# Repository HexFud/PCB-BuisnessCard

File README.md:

## PCB-Badge

I built this electronic badge that can be used for example in hachatons or other IT event if you open the project on KICAD you can also customize the writings.

## How this was made

This project consists only of one PCB 85x100mm and other components like the led matrix controller the microcontoller etc. It also has a NFC tag that can be written with the microcontroller and 2 minigames showed on the 8x8 led matrix on the front.

## How to flash the firmware

1. Install Arduino IDE
   
2. Add the board package going into File -> Preferences and in the additional board URL you paste this https://raw.githubusercontent.com/DeqingSun/ch55xduino/ch55xduino/package_ch55xduino_mcs51_index.json
  
3. Navigate to Tools -> Board -> Boards Manager search ch55xduino and click install
   
4. Plug the microcontroller into the pc and select the correct board you are using in my case a CH552
   
5. You can now flash the firmware

## Notes

If you want to bring your own game on the PCB you're welcome! just fork this repository and then if i'll like your work i am going to mention you guys in the original code. Unfortunatley we only have 2 buttons but in the future I can design another PCB with more functions

## AI decleration

Ai helped me to build the part of the firmware that controls the LED matrix

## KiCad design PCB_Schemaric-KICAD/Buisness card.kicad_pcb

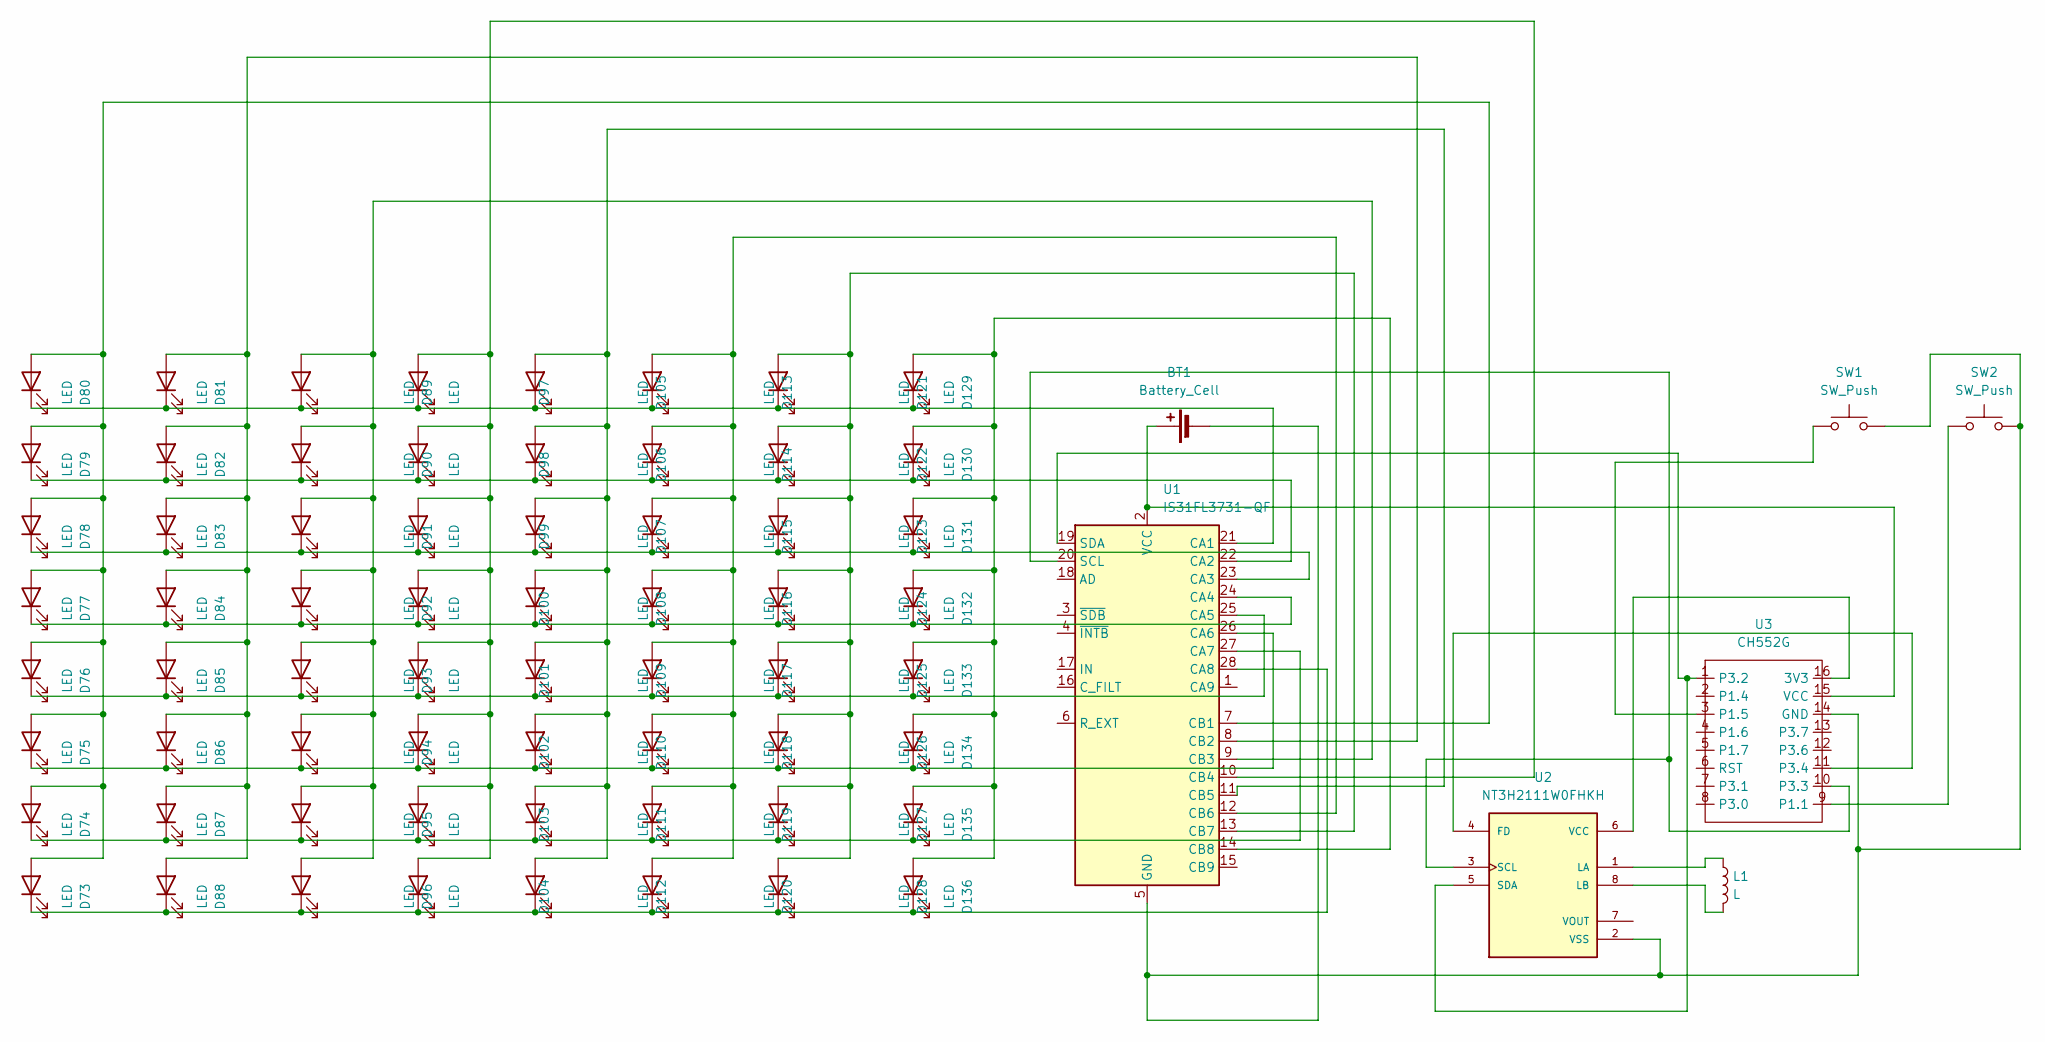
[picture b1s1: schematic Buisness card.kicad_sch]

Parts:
BT1: Battery_Cell; BatteryHolder_Keystone_103_1x20mm
D73, D74, D75, D76, D77, D78, D79, D80, D81, D82, D83, D84, D85, D86, D87, D88, D89, D90, D91, D92, D93, D94, D95, D96, D97, D98, D99, D100, D101, D102, D103, D104, D105, D106, D107, D108, D109, D110, D111, D112, D113, D114, D115, D116, D117, D118, D119, D120, D121, D122, D123, D124, D125, D126, D127, D128, D129, D130, D131, D132, D133, D134, D135, D136: LED; LED_1206_3216Metric
L1: L; COIL_GENERATOR
SW1, SW2: SW_Push; SW_TH_Tactile_Omron_B3F-102x
U1: IS31FL3731-QF; QFN-28-1EP_4x4mm_P0.4mm_EP2.3x2.3mm
U2: NT3H2111W0FHKH; QFN8P50_160X160X50L40X20N
U3: CH552G

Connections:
unnamed: BT1.1 (+), U1.2 (VCC), U3.15 (VCC)
unnamed: BT1.2 (-), SW1.2, SW2.2, U1.5 (GND), U1.29 (GND), U2.2 (VSS), U3.14 (GND)
unnamed: D73.2 (A), D74.2 (A), D75.2 (A), D76.2 (A), D77.2 (A), D78.2 (A), D79.2 (A), D80.2 (A), U1.7 (CB1)
unnamed: D81.2 (A), D82.2 (A), D83.2 (A), D84.2 (A), D85.2 (A), D86.2 (A), D87.2 (A), D88.2 (A), U1.8 (CB2)
unnamed: D89.2 (A), D90.2 (A), D91.2 (A), D92.2 (A), D93.2 (A), D94.2 (A), D95.2 (A), D96.2 (A), U1.9 (CB3)
unnamed: D97.2 (A), D98.2 (A), D99.2 (A), D100.2 (A), D101.2 (A), D102.2 (A), D103.2 (A), D104.2 (A), U1.10 (CB4)
unnamed: D77.1 (K), D84.1 (K), D92.1 (K), D100.1 (K), D108.1 (K), D116.1 (K), D124.1 (K), D132.1 (K), U1.24 (CA4)
unnamed: D76.1 (K), D85.1 (K), D93.1 (K), D101.1 (K), D109.1 (K), D117.1 (K), D125.1 (K), D133.1 (K), U1.25 (CA5)
unnamed: D75.1 (K), D86.1 (K), D94.1 (K), D102.1 (K), D110.1 (K), D118.1 (K), D126.1 (K), D134.1 (K), U1.26 (CA6)
unnamed: D74.1 (K), D87.1 (K), D95.1 (K), D103.1 (K), D111.1 (K), D119.1 (K), D127.1 (K), D135.1 (K), U1.27 (CA7)
unnamed: D73.1 (K), D88.1 (K), D96.1 (K), D104.1 (K), D112.1 (K), D120.1 (K), D128.1 (K), D136.1 (K), U1.28 (CA8)
unnamed: D105.2 (A), D106.2 (A), D107.2 (A), D108.2 (A), D109.2 (A), D110.2 (A), D111.2 (A), D112.2 (A), U1.11 (CB5)
unnamed: D80.1 (K), D81.1 (K), D89.1 (K), D97.1 (K), D105.1 (K), D113.1 (K), D121.1 (K), D129.1 (K), U1.21 (CA1)
unnamed: D79.1 (K), D82.1 (K), D90.1 (K), D98.1 (K), D106.1 (K), D114.1 (K), D122.1 (K), D130.1 (K), U1.22 (CA2)
unnamed: D78.1 (K), D83.1 (K), D91.1 (K), D99.1 (K), D107.1 (K), D115.1 (K), D123.1 (K), D131.1 (K), U1.23 (CA3)
unnamed: D113.2 (A), D114.2 (A), D115.2 (A), D116.2 (A), D117.2 (A), D118.2 (A), D119.2 (A), D120.2 (A), U1.12 (CB6)
unnamed: D121.2 (A), D122.2 (A), D123.2 (A), D124.2 (A), D125.2 (A), D126.2 (A), D127.2 (A), D128.2 (A), U1.13 (CB7)
unnamed: D129.2 (A), D130.2 (A), D131.2 (A), D132.2 (A), D133.2 (A), D134.2 (A), D135.2 (A), D136.2 (A), U1.14 (CB8)
unnamed: U1.20 (SCL), U2.3 (SCL), U3.10 (P3.3)
unnamed: U1.19 (SDA), U2.5 (SDA), U3.1 (P3.2)
unnamed: U2.4 (FD), U3.11 (P3.4)
unnamed: L1.1, U2.1 (LA)
unnamed: L1.2, U2.8 (LB)
unnamed: U2.6 (VCC), U3.16 (3V3)
unnamed: SW2.1, U3.9 (P1.1)
unnamed: SW1.1, U3.3 (P1.5)

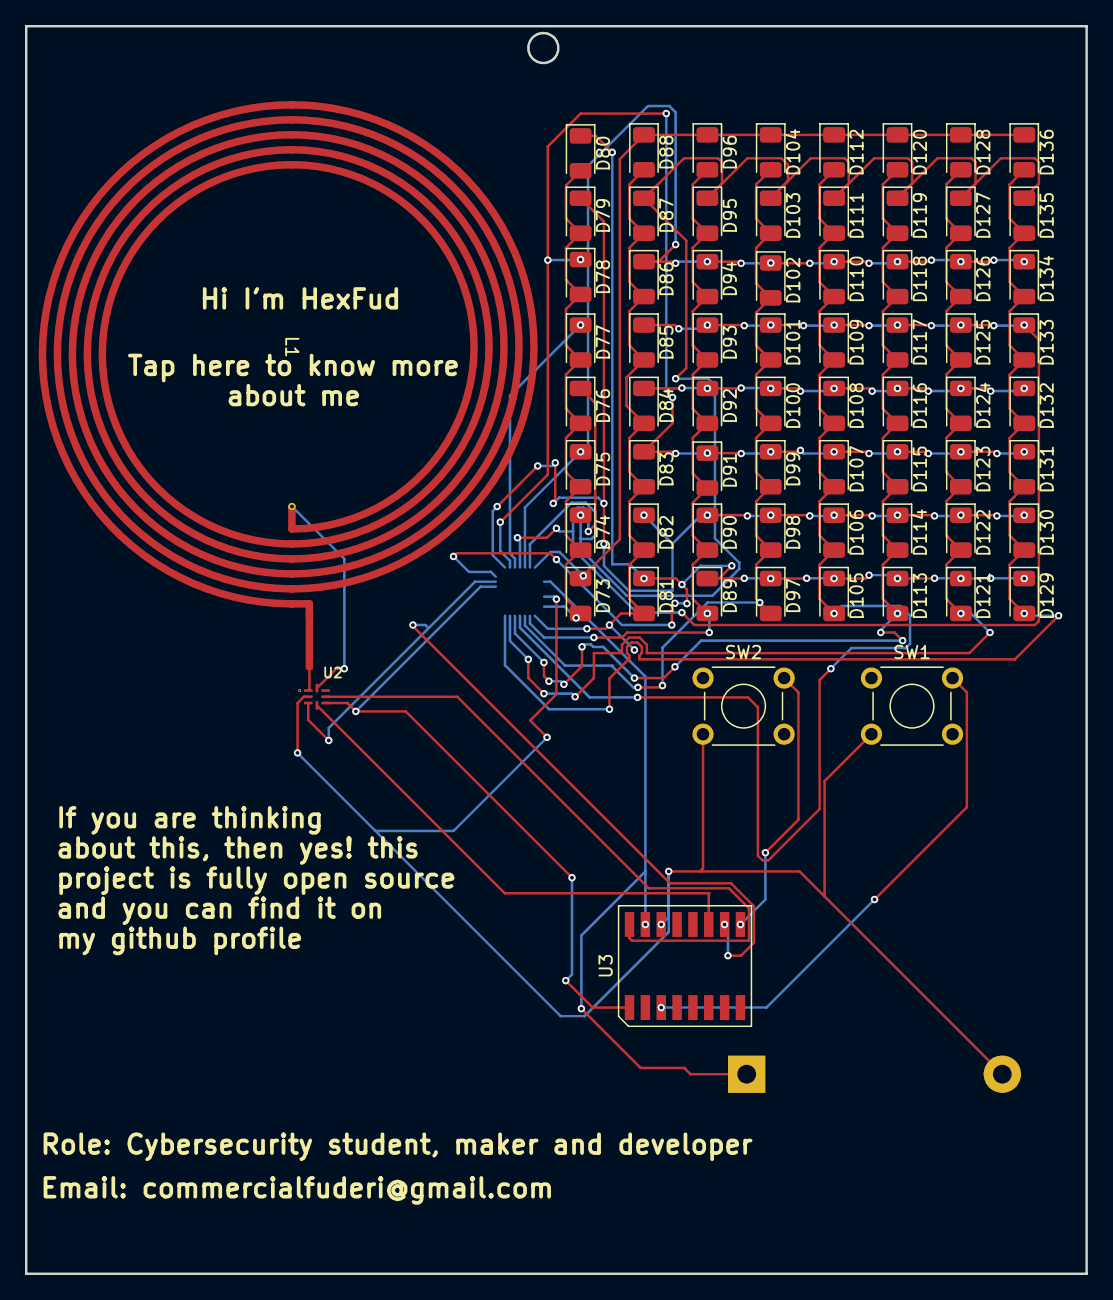
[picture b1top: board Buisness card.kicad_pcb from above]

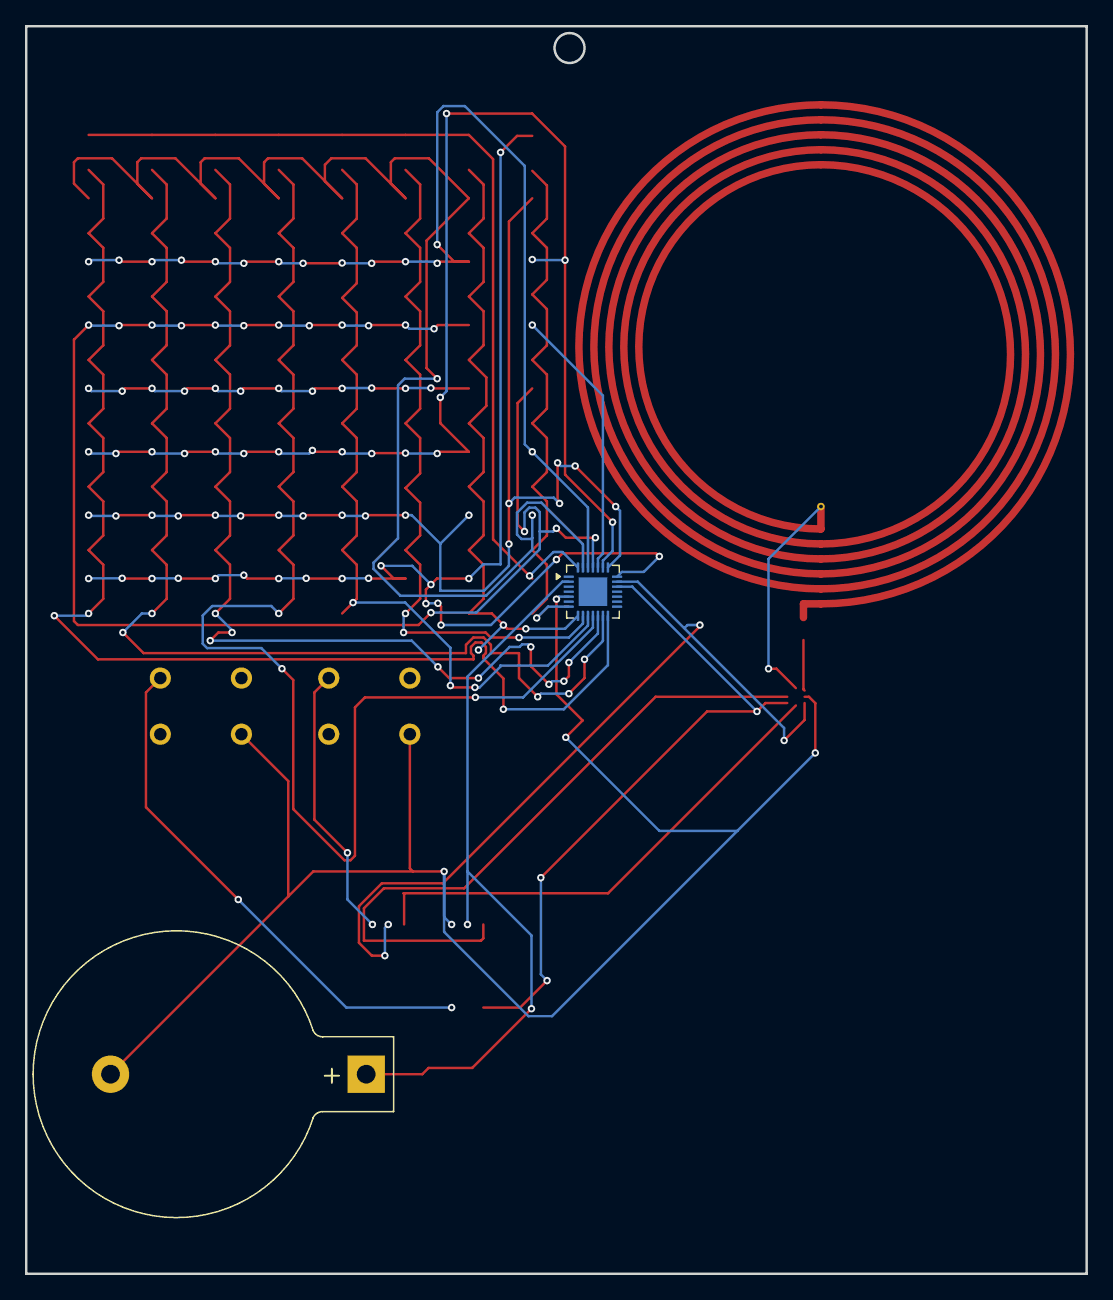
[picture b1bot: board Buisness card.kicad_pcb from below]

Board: 2 copper layers, 85.0 x 100.0 mm, 71 parts (2 on the bottom side), 26 nets.
